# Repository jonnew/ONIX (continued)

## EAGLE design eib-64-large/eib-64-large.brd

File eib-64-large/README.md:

# eib-64-large
64-channel electrode interface board (EIB) with electrical and optical
stimulation. Designed for large animal (e.g. rat) tetrode electrophysiology.
Compatible with [headstage-64](../headstage-64/) and large shuttle-drives.

## Gerber Files
{% include gerber_layers.md %}

## Bill of Materials
The BOM is located on [this google
sheet](https://docs.google.com/spreadsheets/d/1F-KWcdvH_63iXjZf0cgCfDiFX6XXW3qw6rlR8DZrFpQ/edit#gid=1934583654).

## Pinout
The EIB pinout (ADC input mapping, stimulation connections, etc) is located on [this google sheet](https://docs.google.com/spreadsheets/d/11wRDYOqHN5lPb03yUdfXfK0zvaDYsVetplaNK-R90Gg/edit#gid=0)

## Tetrode Connectorization
This EIB uses Neuralynx ["large" gold pins](https://neuralynx.com/hardware/large-eib-pins) to attach tetrode wires. Usage instructions are provided in the [Neuralynx EIB pin Manual](https://neuralynx.com/documents/EIB%20Pins%20Manual.pdf).

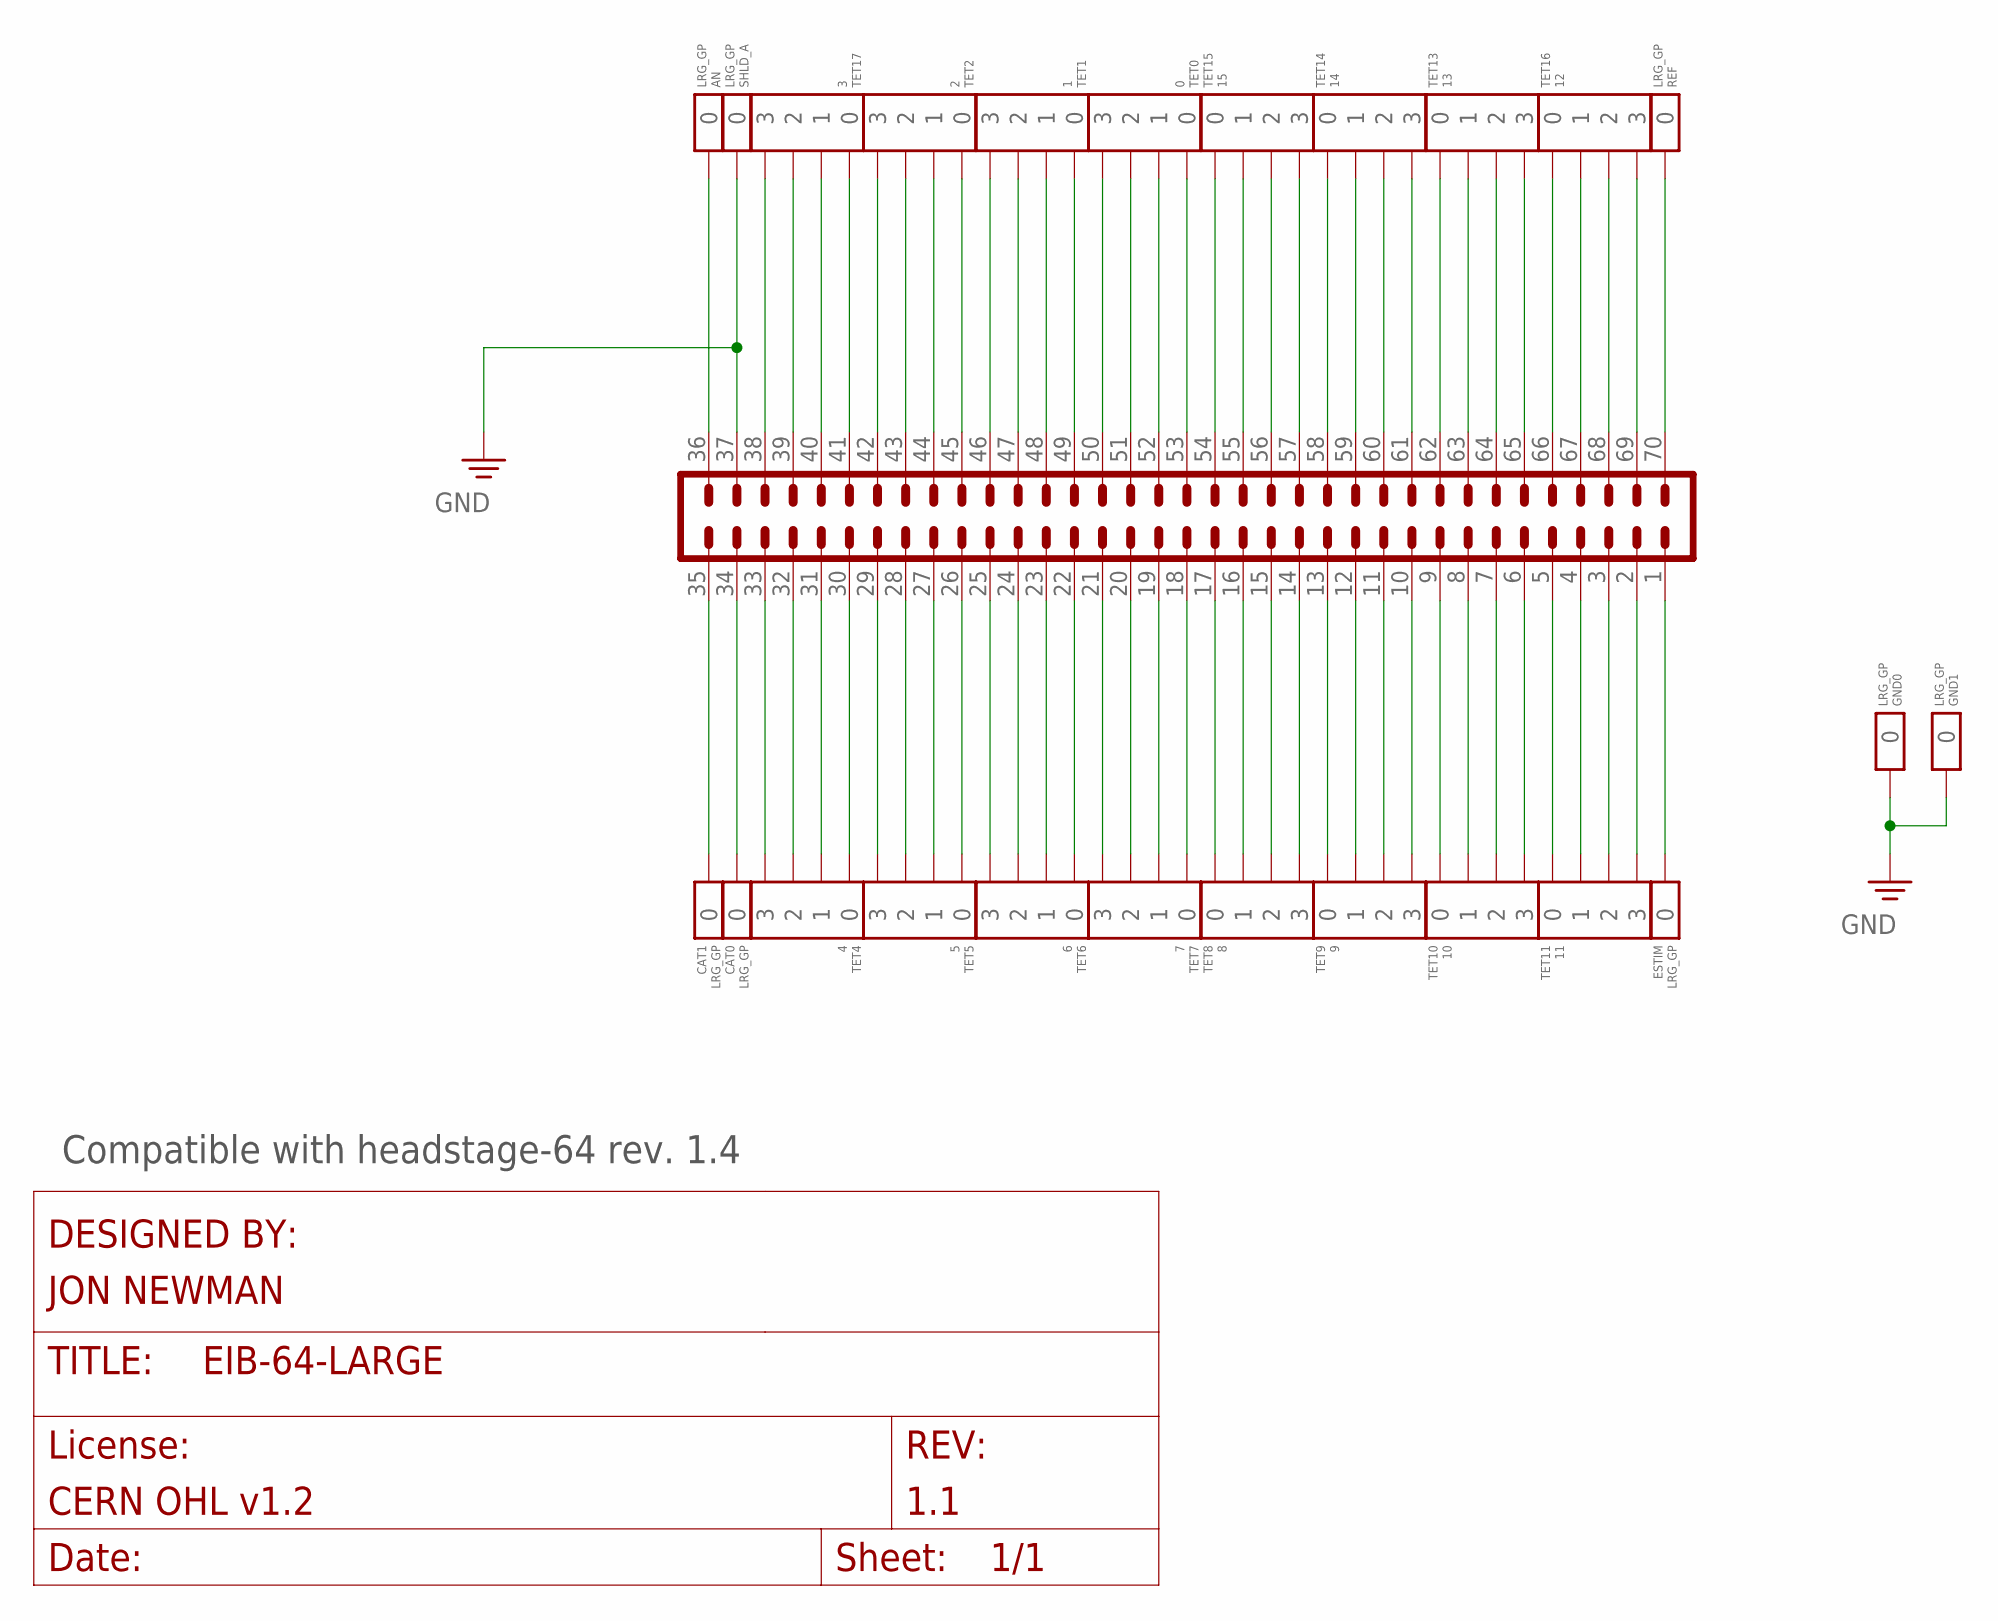
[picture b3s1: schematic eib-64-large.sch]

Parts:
AN: LRG_GP; GOLDPIN_0.5ID_0.7OD
CAT0, CAT1: LRG_GP; GOLDPIN_0.5ID_0.7OD
ESTIM: LRG_GP; GOLDPIN_0.5ID_0.7OD
GND0, GND1: LRG_GP; GOLDPIN_0.5ID_0.7OD
J1: DF40-REC; DDF40-70REC-LRG
REF: LRG_GP; GOLDPIN_0.5ID_0.7OD
SHLD_A: LRG_GP; GOLDPIN_0.5ID_0.7OD
TET0: 0; TETRODE_128_0.5ID_0.7OD
TET1: 1; TETRODE_128_0.5ID_0.7OD
TET2: 2; TETRODE_128_0.5ID_0.7OD
TET4: 4; TETRODE_128_0.5ID_0.7OD
TET5: 5; TETRODE_128_0.5ID_0.7OD
TET6: 6; TETRODE_128_0.5ID_0.7OD
TET7: 7; TETRODE_128_0.5ID_0.7OD
TET8: 8; TETRODE_128_0.5ID_0.7OD
TET9: 9; TETRODE_128_0.5ID_0.7OD
TET10: 10; TETRODE_128_0.5ID_0.7OD
TET11: 11; TETRODE_128_0.5ID_0.7OD
TET13: 13; TETRODE_128_0.5ID_0.7OD
TET14: 14; TETRODE_128_0.5ID_0.7OD
TET15: 15; TETRODE_128_0.5ID_0.7OD
TET16: 12; TETRODE_128_0.5ID_0.7OD
TET17: 3; TETRODE_128_0.5ID_0.7OD

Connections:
AN: AN.P$1, J1.36
CAT0: CAT0.P$1, J1.34
CAT1: CAT1.P$1, J1.35
ESTIM: ESTIM.P$1, J1.1
GND: GND0.P$1, GND1.P$1, J1.37, SHLD_A.P$1
unnamed: J1.69, TET16.3
unnamed: J1.66, TET16.0
unnamed: J1.67, TET16.1
unnamed: J1.68, TET16.2
unnamed: J1.65, TET13.3
unnamed: J1.64, TET13.2
unnamed: J1.63, TET13.1
unnamed: J1.62, TET13.0
unnamed: J1.61, TET14.3
unnamed: J1.60, TET14.2
unnamed: J1.59, TET14.1
unnamed: J1.58, TET14.0
unnamed: J1.57, TET15.3
unnamed: J1.56, TET15.2
unnamed: J1.55, TET15.1
unnamed: J1.54, TET15.0
unnamed: J1.53, TET0.0
unnamed: J1.52, TET0.1
unnamed: J1.51, TET0.2
unnamed: J1.50, TET0.3
unnamed: J1.49, TET1.0
unnamed: J1.48, TET1.1
unnamed: J1.47, TET1.2
unnamed: J1.46, TET1.3
unnamed: J1.45, TET2.0
unnamed: J1.44, TET2.1
unnamed: J1.43, TET2.2
unnamed: J1.42, TET2.3
unnamed: J1.41, TET17.0
unnamed: J1.40, TET17.1
unnamed: J1.39, TET17.2
unnamed: J1.38, TET17.3
unnamed: J1.5, TET11.0
unnamed: J1.4, TET11.1
unnamed: J1.3, TET11.2
unnamed: J1.2, TET11.3
unnamed: J1.33, TET4.3
unnamed: J1.32, TET4.2
unnamed: J1.31, TET4.1
unnamed: J1.30, TET4.0
unnamed: J1.29, TET5.3
unnamed: J1.28, TET5.2
unnamed: J1.27, TET5.1
unnamed: J1.26, TET5.0
unnamed: J1.25, TET6.3
unnamed: J1.24, TET6.2
unnamed: J1.23, TET6.1
unnamed: J1.22, TET6.0
unnamed: J1.21, TET7.3
unnamed: J1.20, TET7.2
unnamed: J1.19, TET7.1
unnamed: J1.18, TET7.0
unnamed: J1.17, TET8.0
unnamed: J1.16, TET8.1
unnamed: J1.15, TET8.2
unnamed: J1.14, TET8.3
unnamed: J1.13, TET9.0
unnamed: J1.12, TET9.1
unnamed: J1.11, TET9.2
unnamed: J1.10, TET9.3
unnamed: J1.9, TET10.0
unnamed: J1.8, TET10.1
unnamed: J1.7, TET10.2
unnamed: J1.6, TET10.3
REF: J1.70, REF.P$1

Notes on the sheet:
Compatible with headstage-64 rev. 1.4

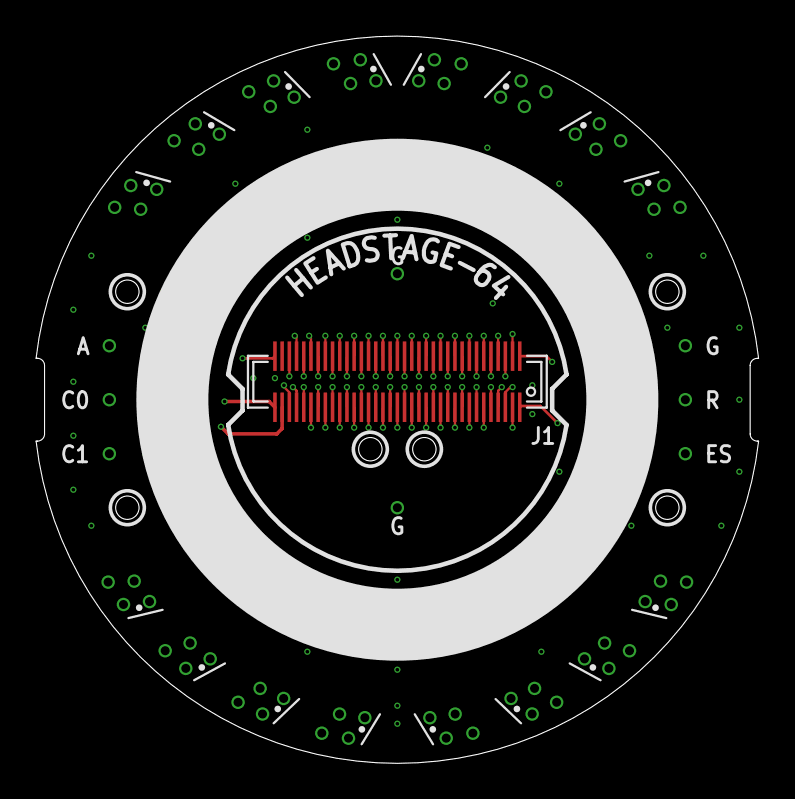
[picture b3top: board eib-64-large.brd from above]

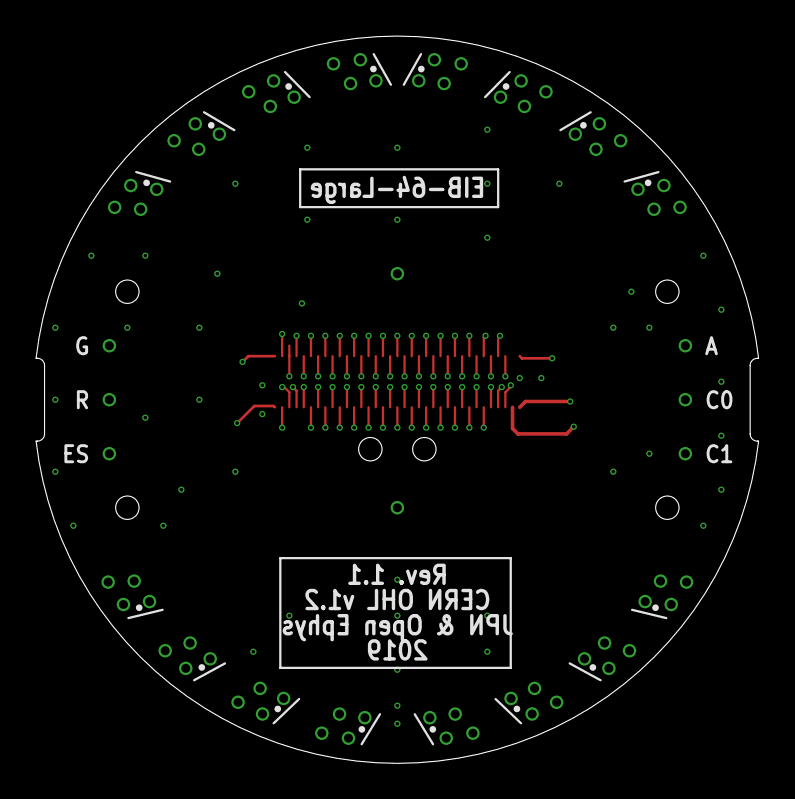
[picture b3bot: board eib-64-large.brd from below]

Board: 4 copper layers, 40.1 x 40.4 mm, 25 parts (8 on the bottom side), 70 nets.

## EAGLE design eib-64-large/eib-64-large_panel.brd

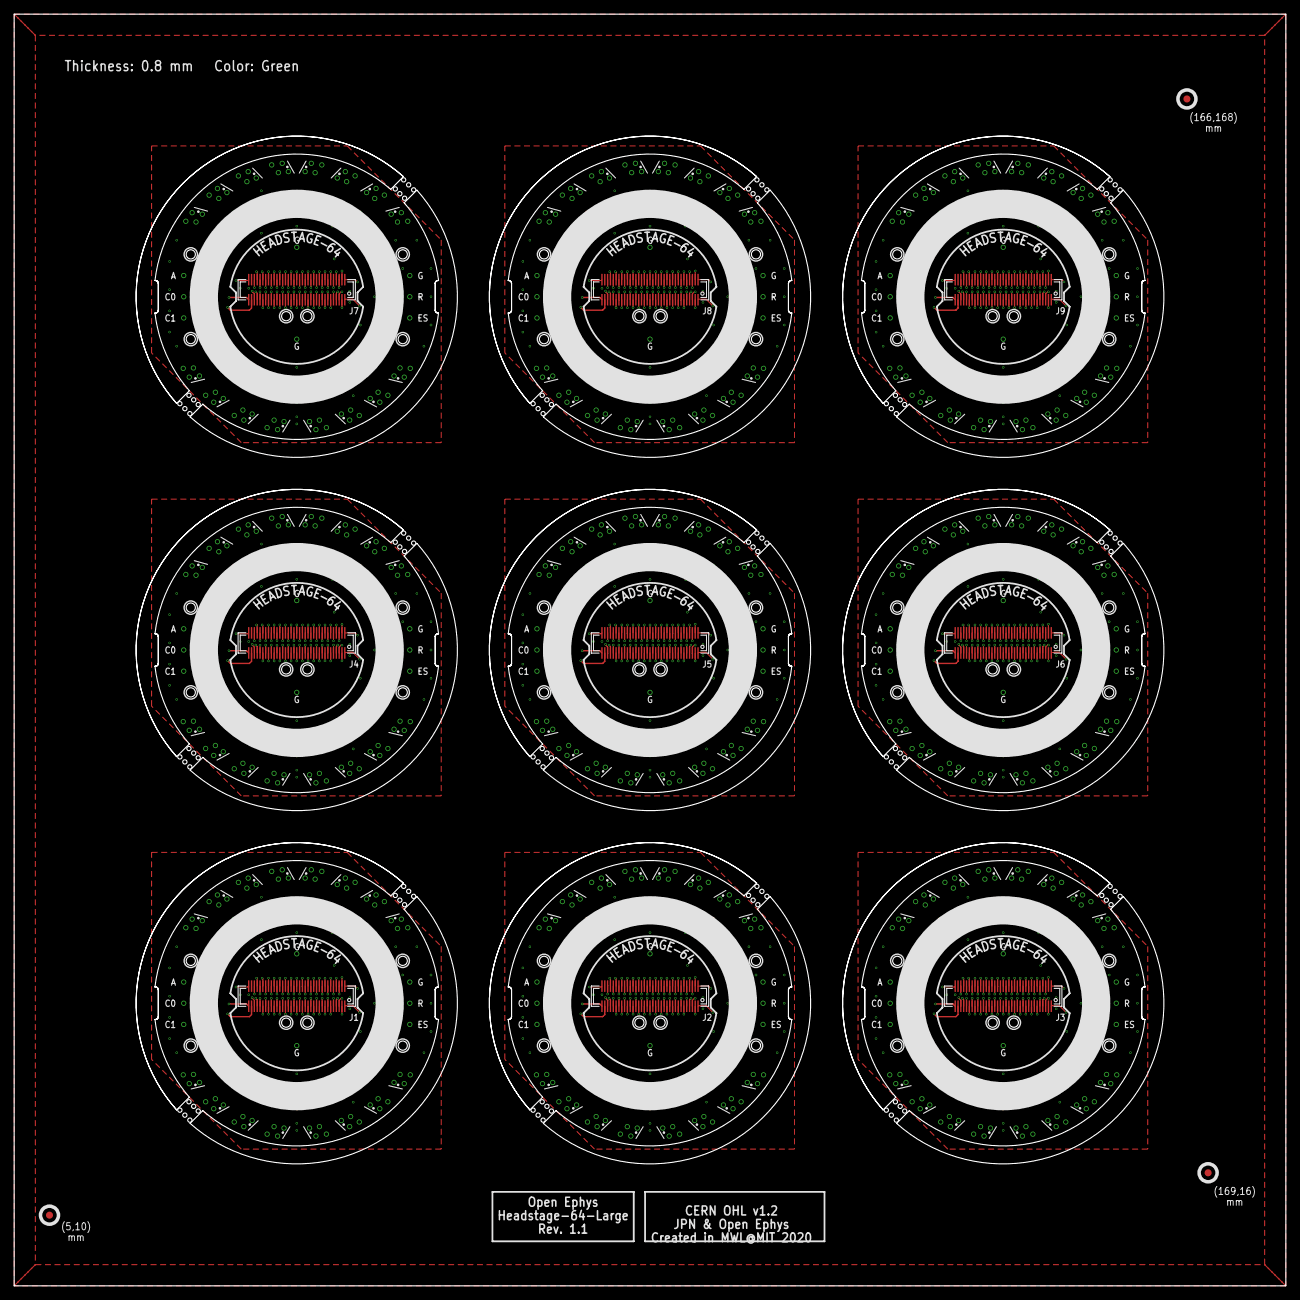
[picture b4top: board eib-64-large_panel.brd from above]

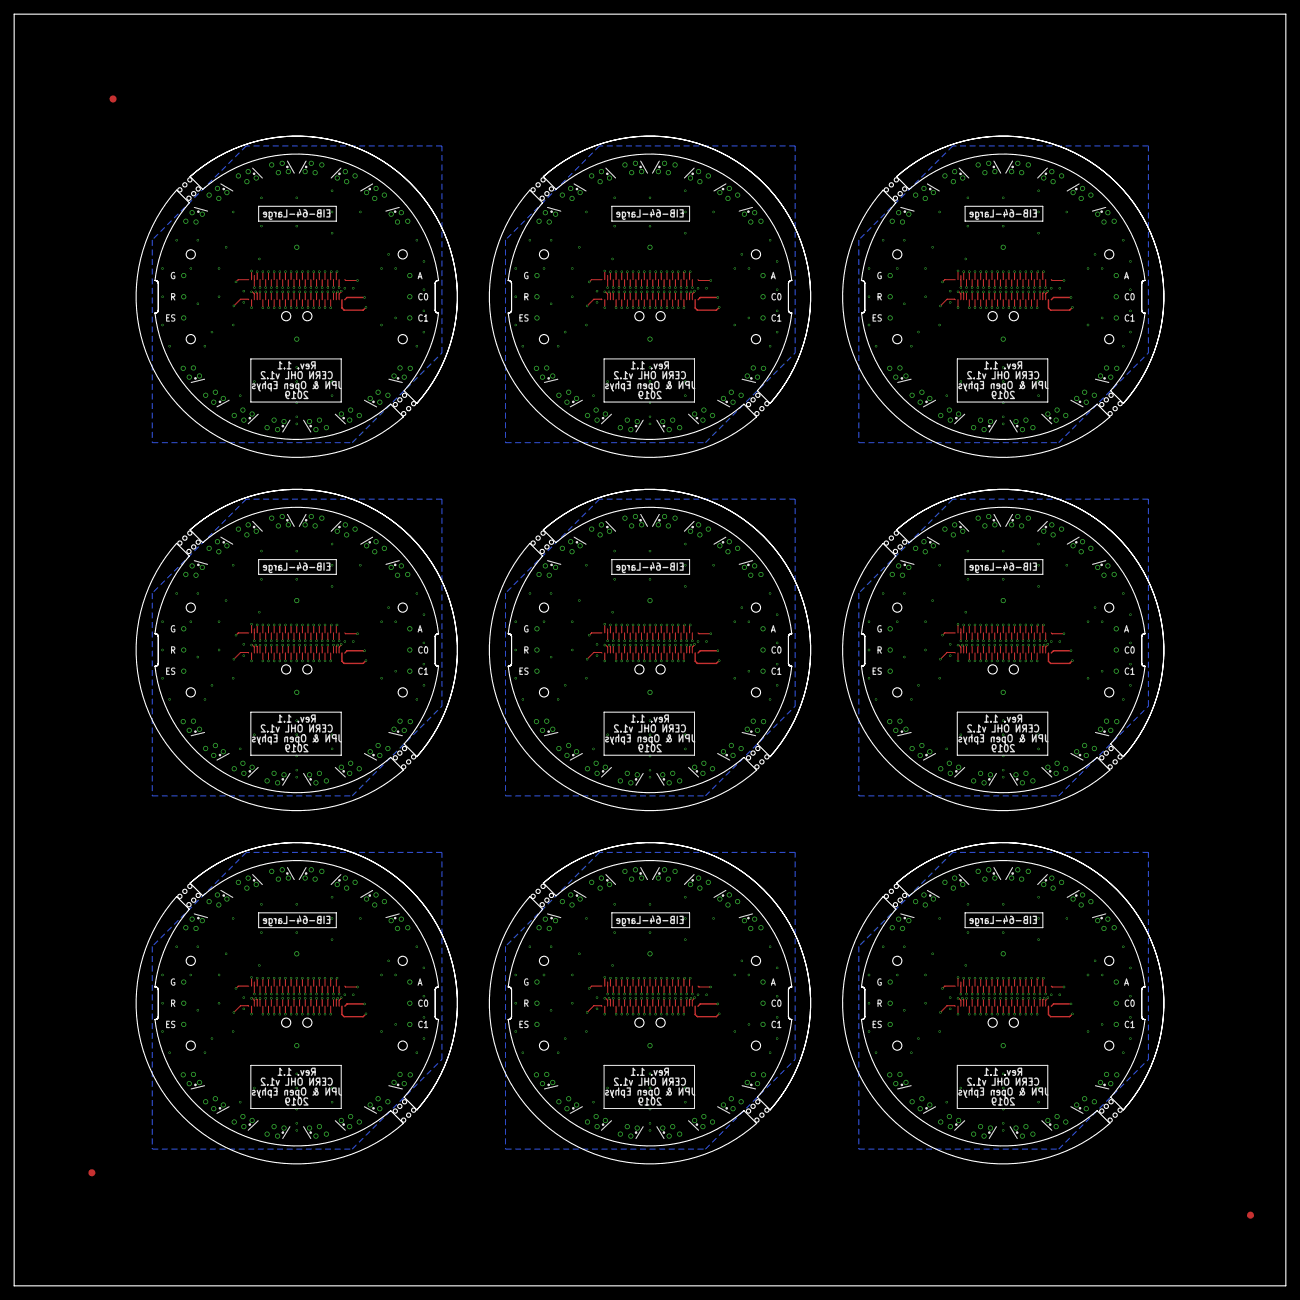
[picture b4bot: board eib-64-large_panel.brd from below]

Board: 4 copper layers, 180.0 x 180.0 mm, 228 parts (72 on the bottom side), 630 nets.

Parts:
AN, AN1, AN2, AN3, AN4, AN5, AN6, AN7, AN8: LRG_GP; GOLDPIN_0.5ID_0.7OD
CAT0, CAT1, CAT2, CAT3, CAT4, CAT5, CAT6, CAT7, CAT8, CAT9, CAT10, CAT11, CAT12, CAT13, CAT14, CAT15, CAT16, CAT17: LRG_GP; GOLDPIN_0.5ID_0.7OD
E$1, E$2, E$3: FIDUCIAL
ESTIM, ESTIM1, ESTIM2, ESTIM3, ESTIM4, ESTIM5, ESTIM6, ESTIM7, ESTIM8: LRG_GP; GOLDPIN_0.5ID_0.7OD
GND0, GND1, GND2, GND3, GND4, GND5, GND6, GND7, GND8, GND9, GND10, GND11, GND12, GND13, GND14, GND15, GND16, GND17: LRG_GP; GOLDPIN_0.5ID_0.7OD
J1, J2, J3, J4, J5, J6, J7, J8, J9: DF40-REC; DDF40-70REC-LRG
REF, REF1, REF2, REF3, REF4, REF5, REF6, REF7, REF8: LRG_GP; GOLDPIN_0.5ID_0.7OD
SHLD_A, SHLD_A1, SHLD_A2, SHLD_A3, SHLD_A4, SHLD_A5, SHLD_A6, SHLD_A7, SHLD_A8: LRG_GP; GOLDPIN_0.5ID_0.7OD
TET0, TET3, TET32, TET48, TET64, TET80, TET96, TET112, TET128: 0; TETRODE_128_0.5ID_0.7OD
TET1, TET12, TET33, TET49, TET65, TET81, TET97, TET113, TET129: 1; TETRODE_128_0.5ID_0.7OD
TET2, TET18, TET34, TET50, TET66, TET82, TET98, TET114, TET130: 2; TETRODE_128_0.5ID_0.7OD
TET4, TET19, TET35, TET51, TET67, TET83, TET99, TET115, TET131: 4; TETRODE_128_0.5ID_0.7OD
TET5, TET20, TET36, TET52, TET68, TET84, TET100, TET116, TET132: 5; TETRODE_128_0.5ID_0.7OD
TET6, TET21, TET37, TET53, TET69, TET85, TET101, TET117, TET133: 6; TETRODE_128_0.5ID_0.7OD
TET7, TET22, TET38, TET54, TET70, TET86, TET102, TET118, TET134: 7; TETRODE_128_0.5ID_0.7OD
TET8, TET29, TET45, TET61, TET77, TET93, TET109, TET125, TET141: 8; TETRODE_128_0.5ID_0.7OD
TET9, TET28, TET44, TET60, TET76, TET92, TET108, TET124, TET140: 9; TETRODE_128_0.5ID_0.7OD
TET10, TET27, TET43, TET59, TET75, TET91, TET107, TET123, TET139: 10; TETRODE_128_0.5ID_0.7OD
TET11, TET26, TET42, TET58, TET74, TET90, TET106, TET122, TET138: 11; TETRODE_128_0.5ID_0.7OD
TET13, TET25, TET41, TET57, TET73, TET89, TET105, TET121, TET137: 13; TETRODE_128_0.5ID_0.7OD
TET14, TET24, TET40, TET56, TET72, TET88, TET104, TET120, TET136: 14; TETRODE_128_0.5ID_0.7OD
TET15, TET23, TET39, TET55, TET71, TET87, TET103, TET119, TET135: 15; TETRODE_128_0.5ID_0.7OD
TET16, TET30, TET46, TET62, TET78, TET94, TET110, TET126, TET142: 12; TETRODE_128_0.5ID_0.7OD
TET17, TET31, TET47, TET63, TET79, TET95, TET111, TET127, TET143: 3; TETRODE_128_0.5ID_0.7OD

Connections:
AN: AN.P$1, J1.36
AN1: AN1.P$1, J2.36
AN2: AN2.P$1, J3.36
AN3: AN3.P$1, J4.36
AN4: AN4.P$1, J5.36
AN5: AN5.P$1, J6.36
AN6: AN6.P$1, J7.36
AN7: AN7.P$1, J8.36
AN8: AN8.P$1, J9.36
CAT0: CAT0.P$1, J1.34
CAT1: CAT1.P$1, J1.35
CAT2: CAT2.P$1, J2.34
CAT3: CAT3.P$1, J2.35
CAT4: CAT4.P$1, J3.34
CAT5: CAT5.P$1, J3.35
CAT6: CAT6.P$1, J4.34
CAT7: CAT7.P$1, J4.35
CAT8: CAT8.P$1, J5.34
CAT9: CAT9.P$1, J5.35
CAT10: CAT10.P$1, J6.34
CAT11: CAT11.P$1, J6.35
CAT12: CAT12.P$1, J7.34
CAT13: CAT13.P$1, J7.35
CAT14: CAT14.P$1, J8.34
CAT15: CAT15.P$1, J8.35
CAT16: CAT16.P$1, J9.34
CAT17: CAT17.P$1, J9.35
ESTIM: ESTIM.P$1, J1.1
ESTIM1: ESTIM1.P$1, J2.1
ESTIM2: ESTIM2.P$1, J3.1
ESTIM3: ESTIM3.P$1, J4.1
ESTIM4: ESTIM4.P$1, J5.1
ESTIM5: ESTIM5.P$1, J6.1
ESTIM6: ESTIM6.P$1, J7.1
ESTIM7: ESTIM7.P$1, J8.1
ESTIM8: ESTIM8.P$1, J9.1
GND1: GND0.P$1, GND1.P$1, J1.37, SHLD_A.P$1
GND2: GND2.P$1, GND3.P$1, J2.37, SHLD_A1.P$1
GND3: GND4.P$1, GND5.P$1, J3.37, SHLD_A2.P$1
GND4: GND6.P$1, GND7.P$1, J4.37, SHLD_A3.P$1
GND5: GND8.P$1, GND9.P$1, J5.37, SHLD_A4.P$1
GND6: GND10.P$1, GND11.P$1, J6.37, SHLD_A5.P$1
GND7: GND12.P$1, GND13.P$1, J7.37, SHLD_A6.P$1
GND8: GND14.P$1, GND15.P$1, J8.37, SHLD_A7.P$1
GND9: GND16.P$1, GND17.P$1, J9.37, SHLD_A8.P$1
unnamed: J1.69, TET16.3
unnamed: J1.66, TET16.0
unnamed: J1.67, TET16.1
unnamed: J1.68, TET16.2
unnamed: J1.65, TET13.3
unnamed: J1.64, TET13.2
unnamed: J1.63, TET13.1
unnamed: J1.62, TET13.0
unnamed: J1.61, TET14.3
unnamed: J1.60, TET14.2
unnamed: J1.59, TET14.1
unnamed: J1.58, TET14.0
unnamed: J1.57, TET15.3
unnamed: J1.56, TET15.2
unnamed: J1.55, TET15.1
unnamed: J1.54, TET15.0
unnamed: J1.53, TET0.0
unnamed: J1.52, TET0.1
unnamed: J1.51, TET0.2
unnamed: J1.50, TET0.3
unnamed: J1.49, TET1.0
unnamed: J1.48, TET1.1
unnamed: J1.47, TET1.2
unnamed: J1.46, TET1.3
unnamed: J1.45, TET2.0
unnamed: J1.44, TET2.1
unnamed: J1.43, TET2.2
unnamed: J1.42, TET2.3
unnamed: J1.41, TET17.0
unnamed: J1.40, TET17.1
unnamed: J1.39, TET17.2
unnamed: J1.38, TET17.3
unnamed: J1.5, TET11.0
unnamed: J1.4, TET11.1
unnamed: J1.3, TET11.2
unnamed: J1.2, TET11.3
unnamed: J2.33, TET19.3
unnamed: J2.32, TET19.2
unnamed: J2.31, TET19.1
unnamed: J2.30, TET19.0
unnamed: J2.29, TET20.3
unnamed: J2.28, TET20.2
unnamed: J2.27, TET20.1
unnamed: J2.26, TET20.0
unnamed: J2.25, TET21.3
unnamed: J2.24, TET21.2
unnamed: J2.23, TET21.1
unnamed: J2.22, TET21.0
unnamed: J2.21, TET22.3
unnamed: J2.20, TET22.2
unnamed: J2.19, TET22.1
unnamed: J2.18, TET22.0
unnamed: J2.17, TET29.0
unnamed: J2.16, TET29.1
unnamed: J2.15, TET29.2
unnamed: J2.14, TET29.3
unnamed: J2.13, TET28.0
unnamed: J2.12, TET28.1
unnamed: J2.11, TET28.2
unnamed: J2.10, TET28.3
unnamed: J2.9, TET27.0
unnamed: J2.8, TET27.1
unnamed: J2.7, TET27.2
unnamed: J2.6, TET27.3
unnamed: J2.69, TET30.3
unnamed: J2.67, TET30.1
unnamed: J2.65, TET25.3
unnamed: J2.64, TET25.2
unnamed: J2.63, TET25.1
unnamed: J2.62, TET25.0
unnamed: J2.61, TET24.3
unnamed: J2.60, TET24.2
unnamed: J2.59, TET24.1
unnamed: J2.58, TET24.0
unnamed: J2.57, TET23.3
unnamed: J2.56, TET23.2
unnamed: J2.55, TET23.1
unnamed: J2.54, TET23.0
unnamed: J2.53, TET3.0
unnamed: J2.52, TET3.1
unnamed: J2.51, TET3.2
unnamed: J2.50, TET3.3
unnamed: J2.49, TET12.0
unnamed: J2.48, TET12.1
unnamed: J2.47, TET12.2
unnamed: J2.46, TET12.3
unnamed: J2.45, TET18.0
unnamed: J2.44, TET18.1
unnamed: J2.43, TET18.2
unnamed: J2.42, TET18.3
unnamed: J2.41, TET31.0
unnamed: J2.39, TET31.2
unnamed: J2.5, TET26.0
unnamed: J2.4, TET26.1
unnamed: J2.3, TET26.2
unnamed: J2.2, TET26.3
unnamed: J2.66, TET30.0
unnamed: J2.68, TET30.2
unnamed: J2.40, TET31.1
unnamed: J2.38, TET31.3
unnamed: J3.33, TET35.3
unnamed: J3.32, TET35.2
unnamed: J3.31, TET35.1
unnamed: J3.30, TET35.0
unnamed: J3.29, TET36.3
unnamed: J3.28, TET36.2
unnamed: J3.27, TET36.1
unnamed: J3.26, TET36.0
unnamed: J3.25, TET37.3
unnamed: J3.24, TET37.2
unnamed: J3.23, TET37.1
unnamed: J3.22, TET37.0
unnamed: J3.21, TET38.3
unnamed: J3.20, TET38.2
unnamed: J3.19, TET38.1
unnamed: J3.18, TET38.0
unnamed: J3.17, TET45.0
unnamed: J3.16, TET45.1
unnamed: J3.15, TET45.2
unnamed: J3.14, TET45.3
unnamed: J3.13, TET44.0
unnamed: J3.12, TET44.1
unnamed: J3.11, TET44.2
unnamed: J3.10, TET44.3
unnamed: J3.9, TET43.0
unnamed: J3.8, TET43.1
unnamed: J3.7, TET43.2
unnamed: J3.6, TET43.3
unnamed: J3.69, TET46.3
unnamed: J3.67, TET46.1
unnamed: J3.65, TET41.3
unnamed: J3.64, TET41.2
unnamed: J3.63, TET41.1
unnamed: J3.62, TET41.0
unnamed: J3.61, TET40.3
unnamed: J3.60, TET40.2
unnamed: J3.59, TET40.1
unnamed: J3.58, TET40.0
unnamed: J3.57, TET39.3
unnamed: J3.56, TET39.2
unnamed: J3.55, TET39.1
unnamed: J3.54, TET39.0
unnamed: J3.53, TET32.0
unnamed: J3.52, TET32.1
unnamed: J3.51, TET32.2
unnamed: J3.50, TET32.3
unnamed: J3.49, TET33.0
unnamed: J3.48, TET33.1
unnamed: J3.47, TET33.2
unnamed: J3.46, TET33.3
unnamed: J3.45, TET34.0
unnamed: J3.44, TET34.1
unnamed: J3.43, TET34.2
unnamed: J3.42, TET34.3
unnamed: J3.41, TET47.0
unnamed: J3.39, TET47.2
unnamed: J3.5, TET42.0
unnamed: J3.4, TET42.1
unnamed: J3.3, TET42.2
unnamed: J3.2, TET42.3
unnamed: J3.66, TET46.0
unnamed: J3.68, TET46.2
unnamed: J3.40, TET47.1
unnamed: J3.38, TET47.3
unnamed: J4.33, TET51.3
unnamed: J4.32, TET51.2
unnamed: J4.31, TET51.1
unnamed: J4.30, TET51.0
unnamed: J4.29, TET52.3
unnamed: J4.28, TET52.2
unnamed: J4.27, TET52.1
unnamed: J4.26, TET52.0
unnamed: J4.25, TET53.3
unnamed: J4.24, TET53.2
unnamed: J4.23, TET53.1
unnamed: J4.22, TET53.0
unnamed: J4.21, TET54.3
unnamed: J4.20, TET54.2
unnamed: J4.19, TET54.1
unnamed: J4.18, TET54.0
unnamed: J4.17, TET61.0
unnamed: J4.16, TET61.1
unnamed: J4.15, TET61.2
unnamed: J4.14, TET61.3
unnamed: J4.13, TET60.0
unnamed: J4.12, TET60.1
unnamed: J4.11, TET60.2
unnamed: J4.10, TET60.3
unnamed: J4.9, TET59.0
unnamed: J4.8, TET59.1
unnamed: J4.7, TET59.2
unnamed: J4.6, TET59.3
unnamed: J4.69, TET62.3
unnamed: J4.67, TET62.1
unnamed: J4.65, TET57.3
unnamed: J4.64, TET57.2
unnamed: J4.63, TET57.1
unnamed: J4.62, TET57.0
unnamed: J1.33, TET4.3
unnamed: J1.32, TET4.2
unnamed: J1.31, TET4.1
unnamed: J1.30, TET4.0
unnamed: J1.29, TET5.3
unnamed: J1.28, TET5.2
unnamed: J1.27, TET5.1
unnamed: J1.26, TET5.0
unnamed: J1.25, TET6.3
unnamed: J1.24, TET6.2
unnamed: J1.23, TET6.1
unnamed: J1.22, TET6.0
unnamed: J1.21, TET7.3
unnamed: J1.20, TET7.2
unnamed: J1.19, TET7.1
unnamed: J1.18, TET7.0
unnamed: J1.17, TET8.0
unnamed: J1.16, TET8.1
unnamed: J1.15, TET8.2
unnamed: J1.14, TET8.3
unnamed: J1.13, TET9.0
unnamed: J1.12, TET9.1
unnamed: J1.11, TET9.2
unnamed: J1.10, TET9.3
unnamed: J1.9, TET10.0
unnamed: J1.8, TET10.1
unnamed: J1.7, TET10.2
unnamed: J1.6, TET10.3
unnamed: J4.61, TET56.3
unnamed: J4.60, TET56.2
unnamed: J4.59, TET56.1
unnamed: J4.58, TET56.0
unnamed: J4.57, TET55.3
unnamed: J4.56, TET55.2
unnamed: J4.55, TET55.1
unnamed: J4.54, TET55.0
unnamed: J4.53, TET48.0
unnamed: J4.52, TET48.1
unnamed: J4.51, TET48.2
unnamed: J4.50, TET48.3
unnamed: J4.49, TET49.0
unnamed: J4.48, TET49.1
unnamed: J4.47, TET49.2
unnamed: J4.46, TET49.3
unnamed: J4.45, TET50.0
unnamed: J4.44, TET50.1
unnamed: J4.43, TET50.2
unnamed: J4.42, TET50.3
unnamed: J4.41, TET63.0
unnamed: J4.39, TET63.2
unnamed: J4.5, TET58.0
unnamed: J4.4, TET58.1
unnamed: J4.3, TET58.2
unnamed: J4.2, TET58.3
unnamed: J4.66, TET62.0
unnamed: J4.68, TET62.2
unnamed: J4.40, TET63.1
unnamed: J4.38, TET63.3
unnamed: J5.33, TET67.3
unnamed: J5.32, TET67.2
unnamed: J5.31, TET67.1
unnamed: J5.30, TET67.0
unnamed: J5.29, TET68.3
unnamed: J5.28, TET68.2
unnamed: J5.27, TET68.1
unnamed: J5.26, TET68.0
unnamed: J5.25, TET69.3
unnamed: J5.24, TET69.2
unnamed: J5.23, TET69.1
unnamed: J5.22, TET69.0
unnamed: J5.21, TET70.3
unnamed: J5.20, TET70.2
unnamed: J5.19, TET70.1
unnamed: J5.18, TET70.0
unnamed: J5.17, TET77.0
unnamed: J5.16, TET77.1
unnamed: J5.15, TET77.2
unnamed: J5.14, TET77.3
unnamed: J5.13, TET76.0
unnamed: J5.12, TET76.1
unnamed: J5.11, TET76.2
unnamed: J5.10, TET76.3
unnamed: J5.9, TET75.0
unnamed: J5.8, TET75.1
unnamed: J5.7, TET75.2
unnamed: J5.6, TET75.3
unnamed: J5.69, TET78.3
unnamed: J5.67, TET78.1
unnamed: J5.65, TET73.3
unnamed: J5.64, TET73.2
unnamed: J5.63, TET73.1
unnamed: J5.62, TET73.0
unnamed: J5.61, TET72.3
unnamed: J5.60, TET72.2
unnamed: J5.59, TET72.1
unnamed: J5.58, TET72.0
unnamed: J5.57, TET71.3
unnamed: J5.56, TET71.2
unnamed: J5.55, TET71.1
unnamed: J5.54, TET71.0
unnamed: J5.53, TET64.0
unnamed: J5.52, TET64.1
unnamed: J5.51, TET64.2
unnamed: J5.50, TET64.3
unnamed: J5.49, TET65.0
unnamed: J5.48, TET65.1
unnamed: J5.47, TET65.2
unnamed: J5.46, TET65.3
unnamed: J5.45, TET66.0
unnamed: J5.44, TET66.1
unnamed: J5.43, TET66.2
unnamed: J5.42, TET66.3
unnamed: J5.41, TET79.0
unnamed: J5.39, TET79.2
unnamed: J5.5, TET74.0
unnamed: J5.4, TET74.1
unnamed: J5.3, TET74.2
unnamed: J5.2, TET74.3
unnamed: J5.66, TET78.0
unnamed: J5.68, TET78.2
unnamed: J5.40, TET79.1
unnamed: J5.38, TET79.3
unnamed: J6.33, TET83.3
unnamed: J6.32, TET83.2
unnamed: J6.31, TET83.1
unnamed: J6.30, TET83.0
unnamed: J6.29, TET84.3
unnamed: J6.28, TET84.2
unnamed: J6.27, TET84.1
unnamed: J6.26, TET84.0
unnamed: J6.25, TET85.3
unnamed: J6.24, TET85.2
unnamed: J6.23, TET85.1
unnamed: J6.22, TET85.0
unnamed: J6.21, TET86.3
unnamed: J6.20, TET86.2
unnamed: J6.19, TET86.1
unnamed: J6.18, TET86.0
unnamed: J6.17, TET93.0
unnamed: J6.16, TET93.1
unnamed: J6.15, TET93.2
unnamed: J6.14, TET93.3
unnamed: J6.13, TET92.0
unnamed: J6.12, TET92.1
unnamed: J6.11, TET92.2
unnamed: J6.10, TET92.3
unnamed: J6.9, TET91.0
unnamed: J6.8, TET91.1
unnamed: J6.7, TET91.2
unnamed: J6.6, TET91.3
unnamed: J6.69, TET94.3
unnamed: J6.67, TET94.1
unnamed: J6.65, TET89.3
unnamed: J6.64, TET89.2
unnamed: J6.63, TET89.1
unnamed: J6.62, TET89.0
unnamed: J6.61, TET88.3
unnamed: J6.60, TET88.2
unnamed: J6.59, TET88.1
unnamed: J6.58, TET88.0
unnamed: J6.57, TET87.3
unnamed: J6.56, TET87.2
unnamed: J6.55, TET87.1
unnamed: J6.54, TET87.0
unnamed: J6.53, TET80.0
unnamed: J6.52, TET80.1
unnamed: J6.51, TET80.2
unnamed: J6.50, TET80.3
unnamed: J6.49, TET81.0
unnamed: J6.48, TET81.1
unnamed: J6.47, TET81.2
unnamed: J6.46, TET81.3
unnamed: J6.45, TET82.0
unnamed: J6.44, TET82.1
unnamed: J6.43, TET82.2
unnamed: J6.42, TET82.3
unnamed: J6.41, TET95.0
unnamed: J6.39, TET95.2
unnamed: J6.5, TET90.0
unnamed: J6.4, TET90.1
unnamed: J6.3, TET90.2
unnamed: J6.2, TET90.3
unnamed: J6.66, TET94.0
unnamed: J6.68, TET94.2
unnamed: J6.40, TET95.1
unnamed: J6.38, TET95.3
unnamed: J7.33, TET99.3
unnamed: J7.32, TET99.2
unnamed: J7.31, TET99.1
unnamed: J7.30, TET99.0
unnamed: J7.29, TET100.3
unnamed: J7.28, TET100.2
unnamed: J7.27, TET100.1
unnamed: J7.26, TET100.0
unnamed: J7.25, TET101.3
unnamed: J7.24, TET101.2
unnamed: J7.23, TET101.1
unnamed: J7.22, TET101.0
unnamed: J7.21, TET102.3
unnamed: J7.20, TET102.2
unnamed: J7.19, TET102.1
unnamed: J7.18, TET102.0
unnamed: J7.17, TET109.0
unnamed: J7.16, TET109.1
unnamed: J7.15, TET109.2
unnamed: J7.14, TET109.3
unnamed: J7.13, TET108.0
unnamed: J7.12, TET108.1
unnamed: J7.11, TET108.2
unnamed: J7.10, TET108.3
unnamed: J7.9, TET107.0
unnamed: J7.8, TET107.1
unnamed: J7.7, TET107.2
unnamed: J7.6, TET107.3
unnamed: J7.69, TET110.3
unnamed: J7.67, TET110.1
unnamed: J7.65, TET105.3
unnamed: J7.64, TET105.2
unnamed: J7.63, TET105.1
unnamed: J7.62, TET105.0
unnamed: J7.61, TET104.3
unnamed: J7.60, TET104.2
unnamed: J7.59, TET104.1
unnamed: J7.58, TET104.0
unnamed: J7.57, TET103.3
unnamed: J7.56, TET103.2
unnamed: J7.55, TET103.1
unnamed: J7.54, TET103.0
unnamed: J7.53, TET96.0
unnamed: J7.52, TET96.1
unnamed: J7.51, TET96.2
unnamed: J7.50, TET96.3
unnamed: J7.49, TET97.0
unnamed: J7.48, TET97.1
unnamed: J7.47, TET97.2
unnamed: J7.46, TET97.3
unnamed: J7.45, TET98.0
unnamed: J7.44, TET98.1
unnamed: J7.43, TET98.2
unnamed: J7.42, TET98.3
unnamed: J7.41, TET111.0
unnamed: J7.39, TET111.2
unnamed: J7.5, TET106.0
unnamed: J7.4, TET106.1
unnamed: J7.3, TET106.2
unnamed: J7.2, TET106.3
unnamed: J7.66, TET110.0
unnamed: J7.68, TET110.2
unnamed: J7.40, TET111.1
unnamed: J7.38, TET111.3
unnamed: J8.33, TET115.3
unnamed: J8.32, TET115.2
unnamed: J8.31, TET115.1
unnamed: J8.30, TET115.0
unnamed: J8.29, TET116.3
unnamed: J8.28, TET116.2
unnamed: J8.27, TET116.1
unnamed: J8.26, TET116.0
unnamed: J8.25, TET117.3
unnamed: J8.24, TET117.2
unnamed: J8.23, TET117.1
unnamed: J8.22, TET117.0
unnamed: J8.21, TET118.3
unnamed: J8.20, TET118.2
unnamed: J8.19, TET118.1
unnamed: J8.18, TET118.0
unnamed: J8.17, TET125.0
unnamed: J8.16, TET125.1
unnamed: J8.15, TET125.2
unnamed: J8.14, TET125.3
unnamed: J8.13, TET124.0
unnamed: J8.12, TET124.1
unnamed: J8.11, TET124.2
unnamed: J8.10, TET124.3
unnamed: J8.9, TET123.0
unnamed: J8.8, TET123.1
unnamed: J8.7, TET123.2
unnamed: J8.6, TET123.3
unnamed: J8.69, TET126.3
unnamed: J8.67, TET126.1
unnamed: J8.65, TET121.3
unnamed: J8.64, TET121.2
unnamed: J8.63, TET121.1
unnamed: J8.62, TET121.0
unnamed: J8.61, TET120.3
unnamed: J8.60, TET120.2
unnamed: J8.59, TET120.1
unnamed: J8.58, TET120.0
unnamed: J8.57, TET119.3
unnamed: J8.56, TET119.2
unnamed: J8.55, TET119.1
unnamed: J8.54, TET119.0
unnamed: J8.53, TET112.0
unnamed: J8.52, TET112.1
unnamed: J8.51, TET112.2
unnamed: J8.50, TET112.3
unnamed: J8.49, TET113.0
unnamed: J8.48, TET113.1
unnamed: J8.47, TET113.2
unnamed: J8.46, TET113.3
unnamed: J8.45, TET114.0
unnamed: J8.44, TET114.1
unnamed: J8.43, TET114.2
unnamed: J8.42, TET114.3
unnamed: J8.41, TET127.0
unnamed: J8.39, TET127.2
unnamed: J8.5, TET122.0
unnamed: J8.4, TET122.1
unnamed: J8.3, TET122.2
unnamed: J8.2, TET122.3
unnamed: J8.66, TET126.0
unnamed: J8.68, TET126.2
unnamed: J8.40, TET127.1
unnamed: J8.38, TET127.3
unnamed: J9.33, TET131.3
unnamed: J9.32, TET131.2
unnamed: J9.31, TET131.1
unnamed: J9.30, TET131.0
unnamed: J9.29, TET132.3
unnamed: J9.28, TET132.2
unnamed: J9.27, TET132.1
unnamed: J9.26, TET132.0
unnamed: J9.25, TET133.3
unnamed: J9.24, TET133.2
unnamed: J9.23, TET133.1
unnamed: J9.22, TET133.0
unnamed: J9.21, TET134.3
unnamed: J9.20, TET134.2
unnamed: J9.19, TET134.1
unnamed: J9.18, TET134.0
unnamed: J9.17, TET141.0
unnamed: J9.16, TET141.1
unnamed: J9.15, TET141.2
unnamed: J9.14, TET141.3
unnamed: J9.13, TET140.0
unnamed: J9.12, TET140.1
unnamed: J9.11, TET140.2
unnamed: J9.10, TET140.3
unnamed: J9.9, TET139.0
unnamed: J9.8, TET139.1
unnamed: J9.7, TET139.2
unnamed: J9.6, TET139.3
unnamed: J9.69, TET142.3
unnamed: J9.67, TET142.1
unnamed: J9.65, TET137.3
unnamed: J9.64, TET137.2
unnamed: J9.63, TET137.1
unnamed: J9.62, TET137.0
unnamed: J9.61, TET136.3
unnamed: J9.60, TET136.2
unnamed: J9.59, TET136.1
unnamed: J9.58, TET136.0
unnamed: J9.57, TET135.3
unnamed: J9.56, TET135.2
unnamed: J9.55, TET135.1
unnamed: J9.54, TET135.0
unnamed: J9.53, TET128.0
unnamed: J9.52, TET128.1
unnamed: J9.51, TET128.2
unnamed: J9.50, TET128.3
unnamed: J9.49, TET129.0
unnamed: J9.48, TET129.1
unnamed: J9.47, TET129.2
unnamed: J9.46, TET129.3
unnamed: J9.45, TET130.0
unnamed: J9.44, TET130.1
unnamed: J9.43, TET130.2
unnamed: J9.42, TET130.3
unnamed: J9.41, TET143.0
unnamed: J9.39, TET143.2
unnamed: J9.5, TET138.0
unnamed: J9.4, TET138.1
unnamed: J9.3, TET138.2
unnamed: J9.2, TET138.3
unnamed: J9.66, TET142.0
unnamed: J9.68, TET142.2
unnamed: J9.40, TET143.1
unnamed: J9.38, TET143.3
REF: J1.70, REF.P$1
REF1: J2.70, REF1.P$1
REF2: J3.70, REF2.P$1
REF3: J4.70, REF3.P$1
REF4: J5.70, REF4.P$1
REF5: J6.70, REF5.P$1
REF6: J7.70, REF6.P$1
REF7: J8.70, REF7.P$1
REF8: J9.70, REF8.P$1
